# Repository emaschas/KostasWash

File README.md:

# KostasWash
<h1>AVR based Washing machine controller</h1>
<h2>Object</h2>
This software is a washing machine controller based on an ATMEGA8535.
<h2>Human interface</h2>
The human interface is based on a LCD and a rotary encoder.
<h2>Power interface</h2>
The power interface is based on a 16 relay board.
<h2>Mechanical part</h2>
The washing machine is an old GROENJE WA583 with a broken mechanical programmer.<br>
The diagram and some other information can be found in the "Documentation" folder.
<h2>More details</h2>
See the <i>Wiki</i> pages for more details...

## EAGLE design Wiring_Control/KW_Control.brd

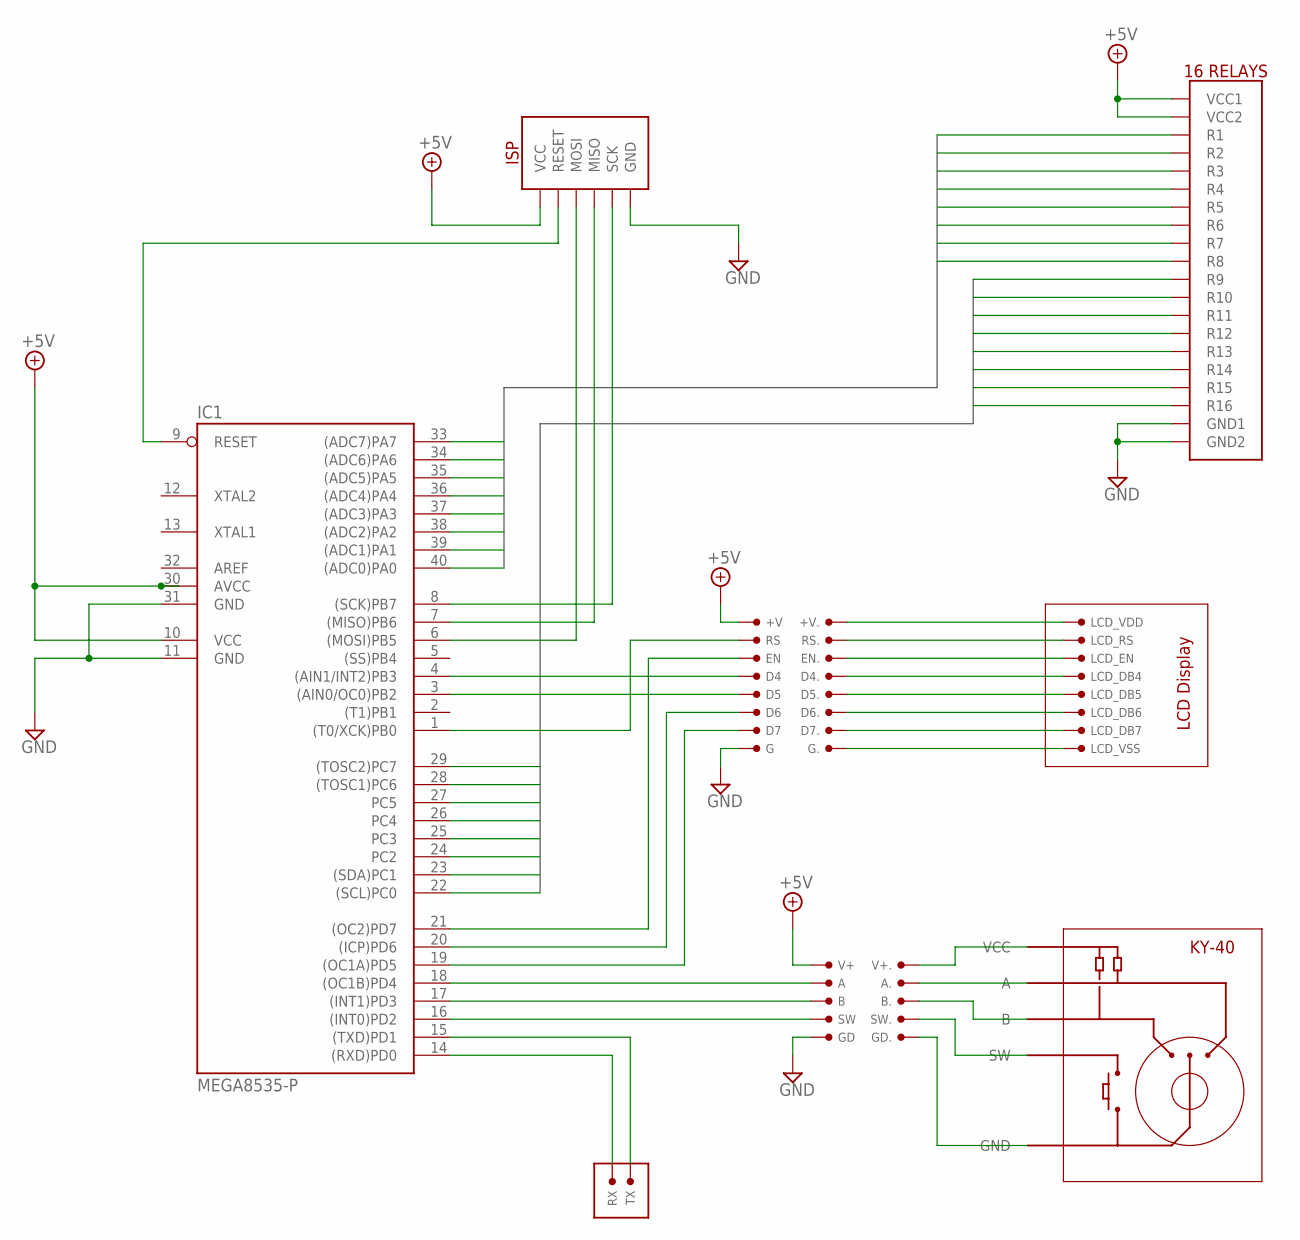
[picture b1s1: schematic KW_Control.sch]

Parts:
+V, +V.: PIN
A, A.: PIN
B, B.: PIN
D4, D4., D5, D5., D6, D6., D7, D7.: PIN
EN, EN.: PIN
G, G.: PIN
GD, GD.: PIN
IC1: MEGA8535-P; DIL40
IC2: KY-40
LCD_DB4, LCD_DB5, LCD_DB6, LCD_DB7: PIN
LCD_EN: PIN
LCD_RS: PIN
LCD_VDD: PIN
LCD_VSS: PIN
RS, RS.: PIN
RX: PIN
SW, SW.: PIN
TX: PIN
U$1: ISP
U$2: RELAYS-16
V+, V+.: PIN

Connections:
+5V: +V.P$1, IC1.10 (VCC), IC1.30 (AVCC), U$1.VCC, U$2.VCC1, U$2.VCC2, V+.P$1
A1: IC1.40 ((ADC0)PA0), U$2.1 (R1)
A2: IC1.39 ((ADC1)PA1), U$2.2 (R2)
A3: IC1.38 ((ADC2)PA2), U$2.3 (R3)
A4: IC1.37 ((ADC3)PA3), U$2.4 (R4)
A5: IC1.36 ((ADC4)PA4), U$2.5 (R5)
A6: IC1.35 ((ADC5)PA5), U$2.6 (R6)
A7: IC1.34 ((ADC6)PA6), U$2.7 (R7)
A8: IC1.33 ((ADC7)PA7), U$2.8 (R8)
B1: IC1.22 ((SCL)PC0), U$2.9 (R9)
B2: IC1.23 ((SDA)PC1), U$2.10 (R10)
B3: IC1.24 (PC2), U$2.11 (R11)
B4: IC1.25 (PC3), U$2.12 (R12)
B5: IC1.26 (PC4), U$2.13 (R13)
B6: IC1.27 (PC5), U$2.14 (R14)
B7: IC1.28 ((TOSC1)PC6), U$2.15 (R15)
B8: IC1.29 ((TOSC2)PC7), U$2.16 (R16)
GND: G.P$1, GD.P$1, IC1.11 (GND), IC1.31 (GND), U$1.GND, U$2.GND1, U$2.GND2
MISO: IC1.7 ((MISO)PB6), U$1.MISO
MOSI: IC1.6 ((MOSI)PB5), U$1.MOSI
unnamed: D7.P$1, IC1.19 ((OC1A)PD5)
unnamed: D6.P$1, IC1.20 ((ICP)PD6)
unnamed: D5.P$1, IC1.3 ((AIN0/OC0)PB2)
unnamed: D4.P$1, IC1.4 ((AIN1/INT2)PB3)
unnamed: +V..P$1, LCD_VDD.P$1
unnamed: G..P$1, LCD_VSS.P$1
unnamed: D4..P$1, LCD_DB4.P$1
unnamed: D7..P$1, LCD_DB7.P$1
unnamed: A.P$1, IC1.18 ((OC1B)PD4)
unnamed: B.P$1, IC1.17 ((INT1)PD3)
unnamed: IC1.16 ((INT0)PD2), SW.P$1
unnamed: A..P$1, IC2.A
unnamed: B..P$1, IC2.B
unnamed: IC2.SW, SW..P$1
unnamed: IC2.VCC, V+..P$1
unnamed: GD..P$1, IC2.GND
unnamed: D6..P$1, LCD_DB6.P$1
unnamed: EN..P$1, LCD_EN.P$1
unnamed: LCD_RS.P$1, RS..P$1
unnamed: D5..P$1, LCD_DB5.P$1
unnamed: EN.P$1, IC1.21 ((OC2)PD7)
unnamed: IC1.1 ((T0/XCK)PB0), RS.P$1
RESET: IC1.9 (RESET), U$1.RESET
RX: IC1.14 ((RXD)PD0), RX.P$1
SCK: IC1.8 ((SCK)PB7), U$1.SCK
TX: IC1.15 ((TXD)PD1), TX.P$1

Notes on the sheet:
LCD Display

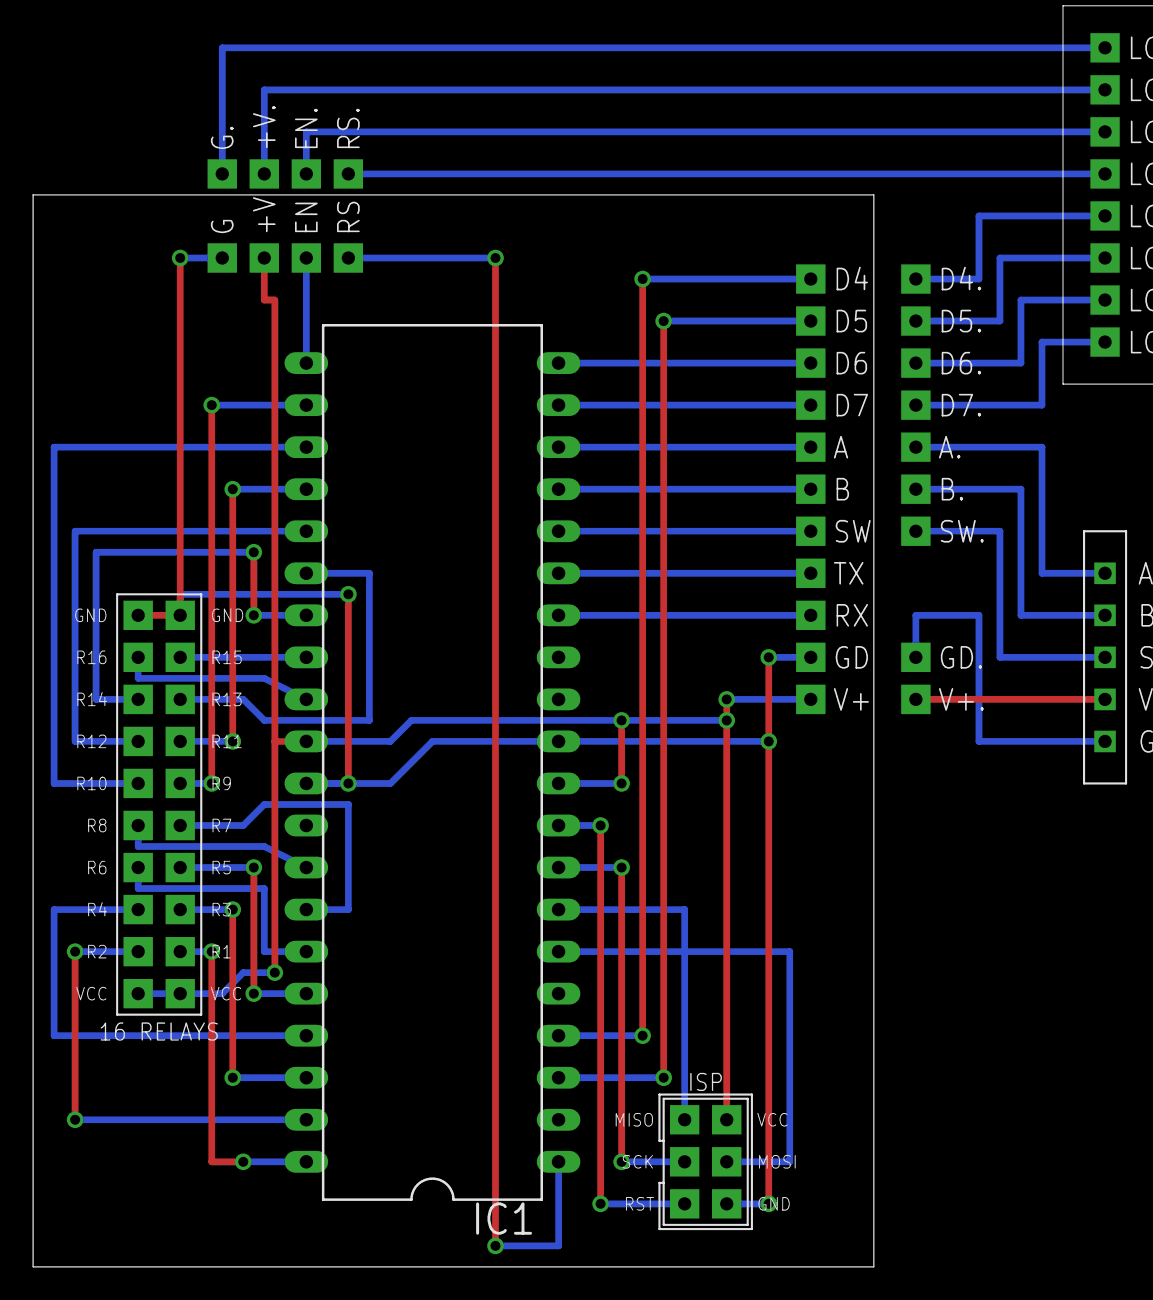
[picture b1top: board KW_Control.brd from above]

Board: 2 copper layers, 50.8 x 64.8 mm, 40 parts (0 on the bottom side), 46 nets.

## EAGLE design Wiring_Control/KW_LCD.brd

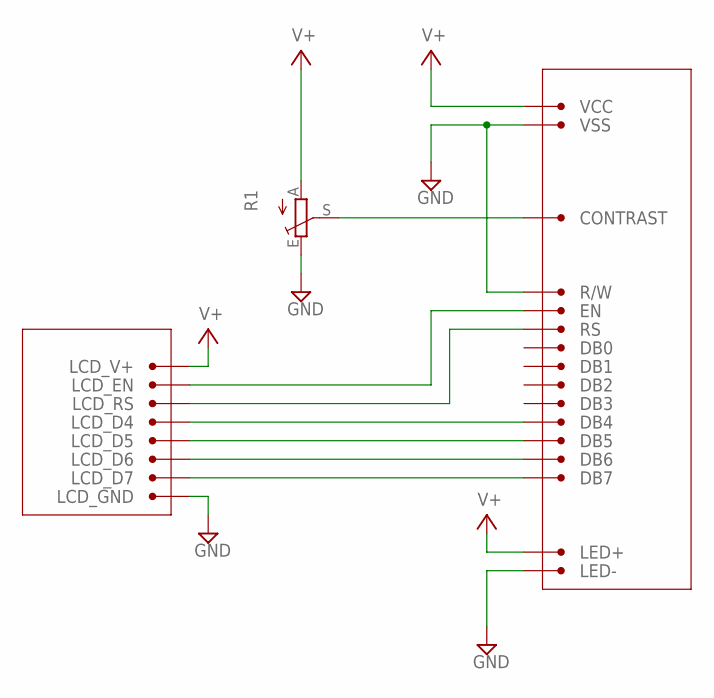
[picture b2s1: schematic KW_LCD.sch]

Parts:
CONTRAST: 3; CONN
DB0: 7; CONN
DB1: 8; CONN
DB2: 9; CONN
DB3: 10; CONN
DB4: 11; CONN
DB5: 12; CONN
DB6: 13; CONN
DB7: 14; CONN
EN: 6; CONN
LCD_D4, LCD_D5, LCD_D6, LCD_D7: 14; CONN
LCD_EN: 14; CONN
LCD_GND: 14; CONN
LCD_RS: 14; CONN
LCD_V+: 14; CONN
LED+: 16; CONN
LED-: 15; CONN
R1: TRIM_EU-ECP10S; ECP10S
R/W: 5; CONN
RS: 4; CONN
VCC: 2; CONN
VSS: 1; CONN

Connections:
GND: LCD_GND.P$1, LED-.P$1, R1.E, R/W.P$1, VSS.P$1
unnamed: DB7.P$1, LCD_D7.P$1
unnamed: DB6.P$1, LCD_D6.P$1
unnamed: LCD_RS.P$1, RS.P$1
unnamed: CONTRAST.P$1, R1.S
unnamed: EN.P$1, LCD_EN.P$1
unnamed: DB5.P$1, LCD_D5.P$1
unnamed: DB4.P$1, LCD_D4.P$1
V+: LCD_V+.P$1, LED+.P$1, R1.A, VCC.P$1

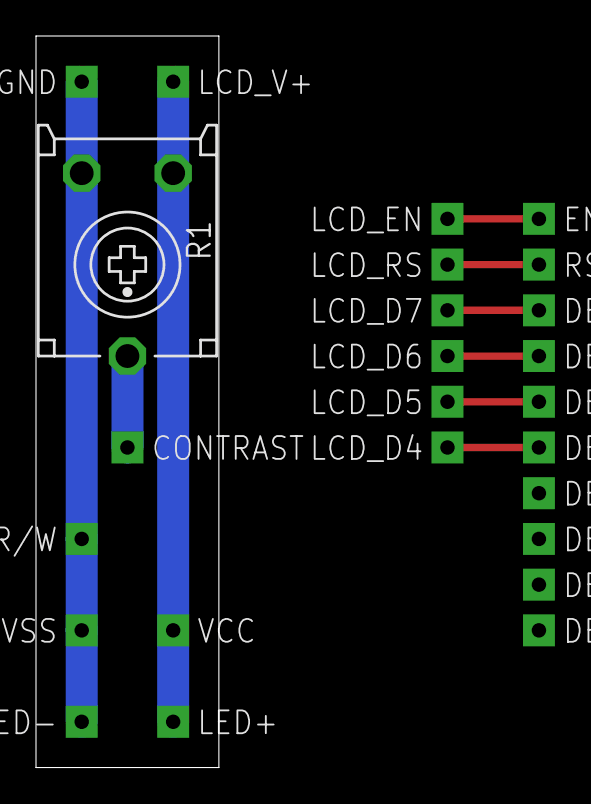
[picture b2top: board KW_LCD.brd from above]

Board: 2 copper layers, 10.2 x 40.6 mm, 25 parts (0 on the bottom side), 9 nets.

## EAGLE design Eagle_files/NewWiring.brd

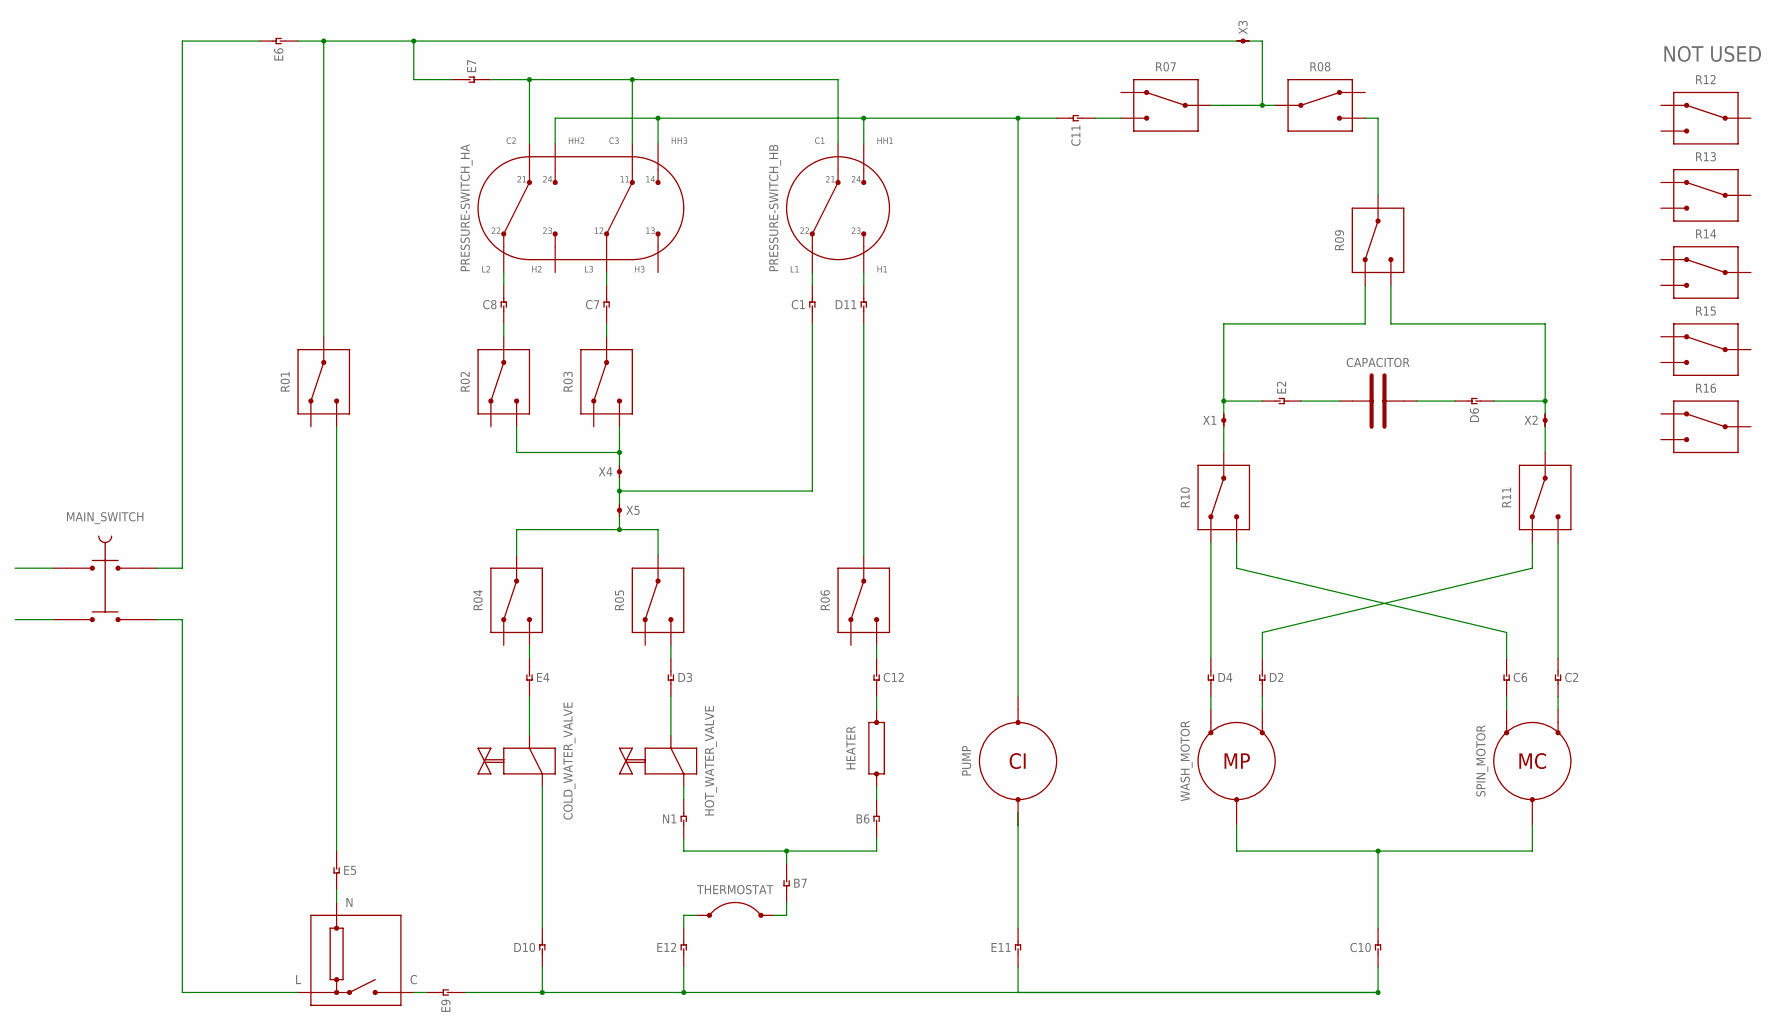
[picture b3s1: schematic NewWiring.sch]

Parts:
B6, B7: CABLE
C1, C2, C6, C7, C8, C10, C11, C12: CABLE
CAPACITOR: CAPACITOR
COLD_WATER_VALVE: VALVE
D2, D3, D4, D6, D10, D11: CABLE
E2, E4, E5, E6, E7, E9, E11, E12: CABLE
HEATER: HEATER
HOT_WATER_VALVE: VALVE
MAIN_SWITCH: SWITCH
N1: CABLE
PRESSURE-SWITCH_HA: PS2
PRESSURE-SWITCH_HB: PS1
PUMP: CI; MOTOR-2
R01, R02, R03, R04, R05, R06, R07, R08, R09, R10, R11, R12, R13, R14, R15, R16: RELAY
SPIN_MOTOR: MC; MOTOR-3
THERMOSTAT: THERMOSTAT
U$1: LOCK
WASH_MOTOR: MP; MOTOR-3
X1, X2, X3, X4, X5: DOMINO

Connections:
C1: C1.P$2 (PIN2), PRESSURE-SWITCH_HB.P$3
C10: C10.P$2 (PIN2), SPIN_MOTOR.MC, WASH_MOTOR.MC
C11-OVERFLOW: C11.P$2 (PIN2), PRESSURE-SWITCH_HA.P$5, PRESSURE-SWITCH_HA.P$8, PRESSURE-SWITCH_HB.P$2, PUMP.M1
D2: D2.P$2 (PIN2), WASH_MOTOR.M3 (M2)
D4: D4.P$2 (PIN2), WASH_MOTOR.M1
D6: CAPACITOR.C2, D6.P$2 (PIN2)
D10: COLD_WATER_VALVE.P$1, D10.P$2 (PIN2)
D11: D11.P$2 (PIN2), PRESSURE-SWITCH_HB.P$4
E5: E5.P$2 (PIN2), U$1.N
E11: E11.P$2 (PIN2), PUMP.M3 (M2)
LIVE: C10.P$1 (PIN1), D10.P$1 (PIN1), E9.P$1 (PIN1), E11.P$1 (PIN1), E12.P$1 (PIN1)
unnamed: E6.P$2 (PIN2), MAIN_SWITCH.O1 (OUT1)
unnamed: COLD_WATER_VALVE.P$2, E4.P$2 (PIN2)
unnamed: MAIN_SWITCH.O2 (OUT2), U$1.L
unnamed: D3.P$2 (PIN2), HOT_WATER_VALVE.P$2
unnamed: B6.P$1 (PIN1), B7.P$1 (PIN1), N1.P$1 (PIN1)
unnamed: E5.P$1 (PIN1), R01.T
unnamed: D4.P$1 (PIN1), R10.R
unnamed: C2.P$1 (PIN1), R11.T
unnamed: C6.P$1 (PIN1), R10.T
unnamed: R08.T, R09.C
unnamed: HOT_WATER_VALVE.P$1, N1.P$2 (PIN2)
unnamed: D2.P$1 (PIN1), R11.R
unnamed: R10.C, X1.P$1 (PIN1)
unnamed: R02.T, R03.T, X4.P$2 (PIN2)
unnamed: C8.P$2 (PIN2), PRESSURE-SWITCH_HA.P$2
unnamed: C7.P$2 (PIN2), PRESSURE-SWITCH_HA.P$6
unnamed: C6.P$2 (PIN2), SPIN_MOTOR.M1
unnamed: E9.P$2 (PIN2), U$1.C
unnamed: C12.P$2 (PIN2), HEATER.H2
unnamed: E12.P$2 (PIN2), THERMOSTAT.T2
unnamed: C12.P$1 (PIN1), R06.T
unnamed: C11.P$1 (PIN1), R07.T
unnamed: D3.P$1 (PIN1), R05.T
unnamed: C2.P$2 (PIN2), SPIN_MOTOR.M3 (M2)
unnamed: E2.P$1 (PIN1), R09.R, X1.P$2 (PIN2)
unnamed: B7.P$2 (PIN2), THERMOSTAT.T1
unnamed: B6.P$2 (PIN2), HEATER.H1
unnamed: D6.P$1 (PIN1), R09.T, X2.P$2 (PIN2)
unnamed: R11.C, X2.P$1 (PIN1)
unnamed: R07.C, R08.C, X3.P$2 (PIN2)
unnamed: CAPACITOR.C1, E2.P$2 (PIN2)
unnamed: R04.C, R05.C, X5.P$2 (PIN2)
unnamed: E7.P$2 (PIN2), PRESSURE-SWITCH_HA.P$1, PRESSURE-SWITCH_HA.P$4, PRESSURE-SWITCH_HB.P$1
unnamed: C8.P$1 (PIN1), R02.C
unnamed: C7.P$1 (PIN1), R03.C
unnamed: D11.P$1 (PIN1), R06.C
unnamed: E4.P$1 (PIN1), R04.T
NEUTRAL: E6.P$1 (PIN1), E7.P$1 (PIN1), R01.C, X3.P$1 (PIN1)
PHASE3: C1.P$1 (PIN1), X4.P$1 (PIN1), X5.P$1 (PIN1)

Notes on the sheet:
NOT USED

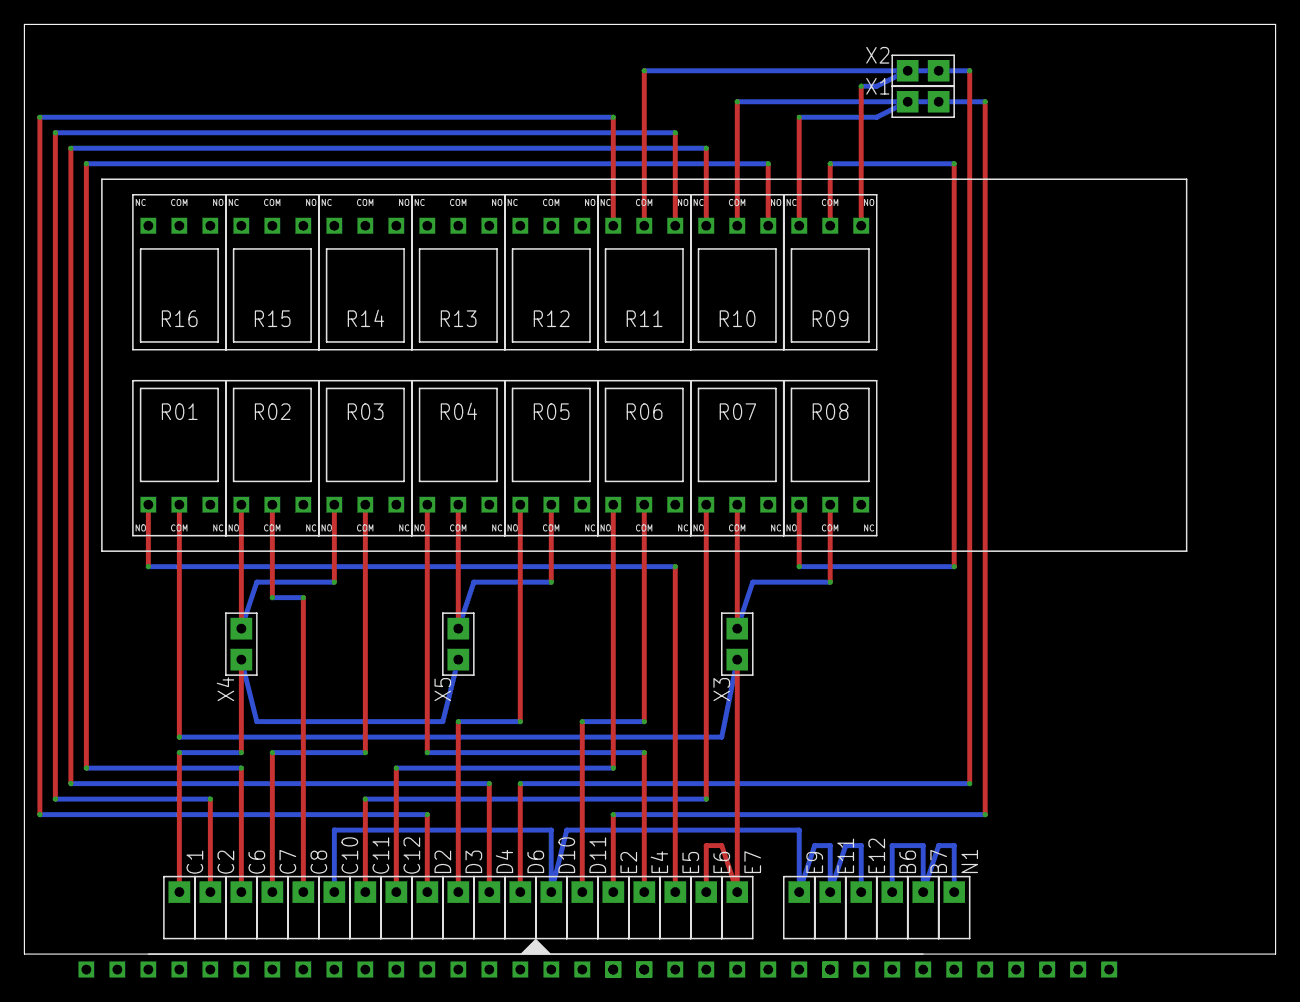
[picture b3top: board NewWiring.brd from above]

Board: 2 copper layers, 102.5 x 76.2 mm, 58 parts (0 on the bottom side), 50 nets.

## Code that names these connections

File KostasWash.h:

/////////////////////////////////////////////
// KostasWash v1.1                         //
// ---------------                         //
// Target CPU : Atmega8535 at 8MHz (int.)  //
/////////////////////////////////////////////

#include <avr/io.h>
#include <avr/interrupt.h>
#include <util/delay.h>
#include <stdio.h>
#include "TIMER.h"
#include "LCD.h"

//-----------------------------------------------------------------------------------
// WIRING
//-----------------------------------------------------------------------------------
// Human Interface
//-----------------------------------------------------------------------------------
// Encoder:
//   PD2 : Switch 
//   PD3 : Clock
//   PD4 : Data
// LCD Display
//   PD7 : LCD_EN
//   PB0 : LCD_RS
//   PB3 : LCD_DB4
//   PB2 : LCD_DB5
//   PD6 : LCD_DB6
//   PD5 : LCD_DB7
//-----------------------------------------------------------------------------------
// Washing machine 
//-----------------------------------------------------------------------------------
//   PA1 : Relay R01
//   PA0 : Relay R02
//   PA3 : Relay R03
//   PA2 : Relay R04
//   PA5 : Relay R05
//   PA4 : Relay R06
//   PA7 : Relay R07
//   PA6 : Relay R08
//   PC7 : Relay R09
//   PC3 : Relay R10
//   PC6 : Relay R11
//   PC2 : Relay R12
//   PC5 : Relay R13
//   PC1 : Relay R14
//   PC4 : Relay R15
//   PC0 : Relay R16
//-----------------------------------------------------------------------------------

#define false   0
#define true  (!0)
#define off     0
#define on      1

// Shared Enumerations
// -------------------
enum SwitchStatus 
{ 
  NO_PRESS,
  SHORT_PRESS,
  LONG_PRESS
};

// Macros for Encoder
// ------------------
#define SWITCH     (PIND  &  _BV(PIND2))
#define ENCODER_A  (PIND  &  _BV(PIND3))
#define ENCODER_B  (PIND  &  _BV(PIND4))

// Macros for Relays
// -----------------
// Inverted logic : 1=relay off 0=relay on
#define RELAY01_OFF()  PORTA |=  _BV(PINA1)
#define RELAY01_ON()   PORTA &= ~_BV(PINA1)
#define RELAY02_OFF()  PORTA |=  _BV(PINA0)
#define RELAY02_ON()   PORTA &= ~_BV(PINA0)
#define RELAY03_OFF()  PORTA |=  _BV(PINA3)
#define RELAY03_ON()   PORTA &= ~_BV(PINA3)
#define RELAY04_OFF()  PORTA |=  _BV(PINA2)
#define RELAY04_ON()   PORTA &= ~_BV(PINA2)
#define RELAY05_OFF()  PORTA |=  _BV(PINA5)
#define RELAY05_ON()   PORTA &= ~_BV(PINA5)
#define RELAY06_OFF()  PORTA |=  _BV(PINA4)
#define RELAY06_ON()   PORTA &= ~_BV(PINA4)
#define RELAY07_OFF()  PORTA |=  _BV(PINA7)
#define RELAY07_ON()   PORTA &= ~_BV(PINA7)
#define RELAY08_OFF()  PORTA |=  _BV(PINA6)
#define RELAY08_ON()   PORTA &= ~_BV(PINA6)
#define RELAY09_OFF()  PORTC |=  _BV(PINC7)
#define RELAY09_ON()   PORTC &= ~_BV(PINC7)
#define RELAY10_OFF()  PORTC |=  _BV(PINC3)
#define RELAY10_ON()   PORTC &= ~_BV(PINC3)
#define RELAY11_OFF()  PORTC |=  _BV(PINC6)
#define RELAY11_ON()   PORTC &= ~_BV(PINC6)
#define RELAY12_OFF()  PORTC |=  _BV(PINC2)
#define RELAY12_ON()   PORTC &= ~_BV(PINC2)
#define RELAY13_OFF()  PORTC |=  _BV(PINC5)
#define RELAY13_ON()   PORTC &= ~_BV(PINC5)
#define RELAY14_OFF()  PORTC |=  _BV(PINC1)
#define RELAY14_ON()   PORTC &= ~_BV(PINC1)
#define RELAY15_OFF()  PORTC |=  _BV(PINC4)
#define RELAY15_ON()   PORTC &= ~_BV(PINC4)
#define RELAY16_OFF()  PORTC |=  _BV(PINC0)
#define RELAY16_ON()   PORTC &= ~_BV(PINC0)

// Masks definition for "step"
// ---------------------------
// PORTA : MSB - PORTC : LSB
#define R01 _BV(1)   // PINA1
#define R02 _BV(0)   // PINA0
#define R03 _BV(3)   // PINA3
#define R04 _BV(2)   // PINA2
#define R05 _BV(5)   // PINA5
#define R06 _BV(4)   // PINA4
#define R07 _BV(7)   // PINA7
#define R08 _BV(6)   // PINA6
#define R09 _BV(7+8) // PINC7
#define R10 _BV(3+8) // PINC3
#define R11 _BV(6+8) // PINC6
#define R12 _BV(2+8) // PINC2
#define R13 _BV(5+8) // PINC5
#define R14 _BV(1+8) // PINC1
#define R15 _BV(4+8) // PINC4
#define R16 _BV(0+8) // PINC0

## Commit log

2018-03-12 Add files via upload
    First version.
2018-03-13 Added files
2018-03-13 Updated wash sequence
2018-03-13 Filter
2018-03-13 Filter on dirs
2018-03-14 Moved definitions Wasign.h
2018-03-14 Separate file for Washing.c
2018-03-14 Update Makefile
2018-03-14 Changed to count down
2018-03-16 Added relay masks
2018-03-16 Change WashStates enum
2018-03-16 Updated wash program
2018-03-17 Updated messages and stop rotation when aborting
2018-03-18 Added menus
2018-03-19 Correct program text
2018-03-19 Updated program matrix
2018-03-19 Corrected display at start
2018-03-20 Rename main.c to Main.c
2018-03-20 Added parameter for long switch press time
2018-03-20 Update version displayed at startup
2018-03-24 Updated relay description
2018-03-25 Added Daigram
2018-03-25 Resized
2018-03-25 Added WA583 Diagram
2018-03-25 Added WA583 wiring
2018-03-25 Translated in English (thanks to google trad.)
2018-03-25 Translated (approximately)
2018-03-25 Corrected diagram
2018-03-26 Enhanced diagram
2018-03-26 Added translated programmer time diagram
2018-03-27 Added 6561 sequences
2018-03-27 Moved files in documentation folder
2018-03-27 Updated sequence
2018-03-27 Added New Schematic
2018-03-30 Added simulator
2018-03-30 Deleted
2018-03-31 New Wiring
2018-04-06 Updeted
2018-04-08 Upated revision
    Test...
2018-04-08 Modified wiring of R08 and R09
2018-04-09 Updated documentation
2018-04-09 Added KostasTest for wiring checking
2018-04-09 Shifted washing program in PROGMEM
2018-04-10 Correction
2018-04-13 Added connectors
2018-04-16 Added picture
2018-04-19 Modified
2018-04-24 Added Cabling
2018-04-27 Improved
2018-04-29 Added Control Wiring
2018-04-30 Housekeeping
2018-05-19 https://github.com/emaschas/KostasWash.git
2018-05-21 Updated.
2018-05-26 Added
2025-05-03 Elecric motor plate
